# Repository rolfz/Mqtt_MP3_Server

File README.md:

# Mqtt MP3 Player based on Wemos-D1 ESP8266 circuit and VS1053 audio module

## Functionality:

	This module was created to be controlled by Node-Red over a MQTT Broker.
	The module understands various tags such as:
			 /Zaudio/play  "file to play with extension" 8.3 format
			 /Zaudio/volume xxx (volume in db) 0 to 100db is possible
			 /Zaudio/command stop (will stop the file played)
			
	The module also allows to connect a Neoled display module with 7 leds
			 /Zaudio/neoled #xxyyzz  (set color in hex rgb format

## Hardware:
	Wemos D1 module, SPI bus used to communicate with audio module
	
	Adafruit VS1053 module with 3W amplifier PRODUCT ID: 3436
	
	Micro SD card 128mB our larger FAT format.
	
	Connections:
			Wemos D1		-      VS1053   -   Neoled
			D8						MISO
			D7						MOSI
			D5						SCK
			D4						SD-CS
			D6						MP3-CS
			D3						DREQ
			DO						XDCS
			D2									IN
			+5V						AUDIO +5V	5V
			+3V						DIGIT.+3V
	
	! Use min. 5V 2Amp USB to supply both circuits + LED's
		
## Software Libraries:

	Adafruit_Neopixel
	Adafruit_VS1053_Library-master
	pubsubclient (MQTT library)
	
## Software Main file:
	mqtt_mp3_server.ino contains all customized code based on the MQTT client example
	wifi_settings.h 	contains the WIFI private setting

## Using the Zaudio module with Node-red
	Zaudio was tested with a connection to an MQTT brocker running on a RPI3 board
		Software installed was Openhabian with MQTT and Node-red modules installed.

	v1.1 rz 21.2.2018	added OTA code
	v1.0 rz 28.1.2018   orginial code

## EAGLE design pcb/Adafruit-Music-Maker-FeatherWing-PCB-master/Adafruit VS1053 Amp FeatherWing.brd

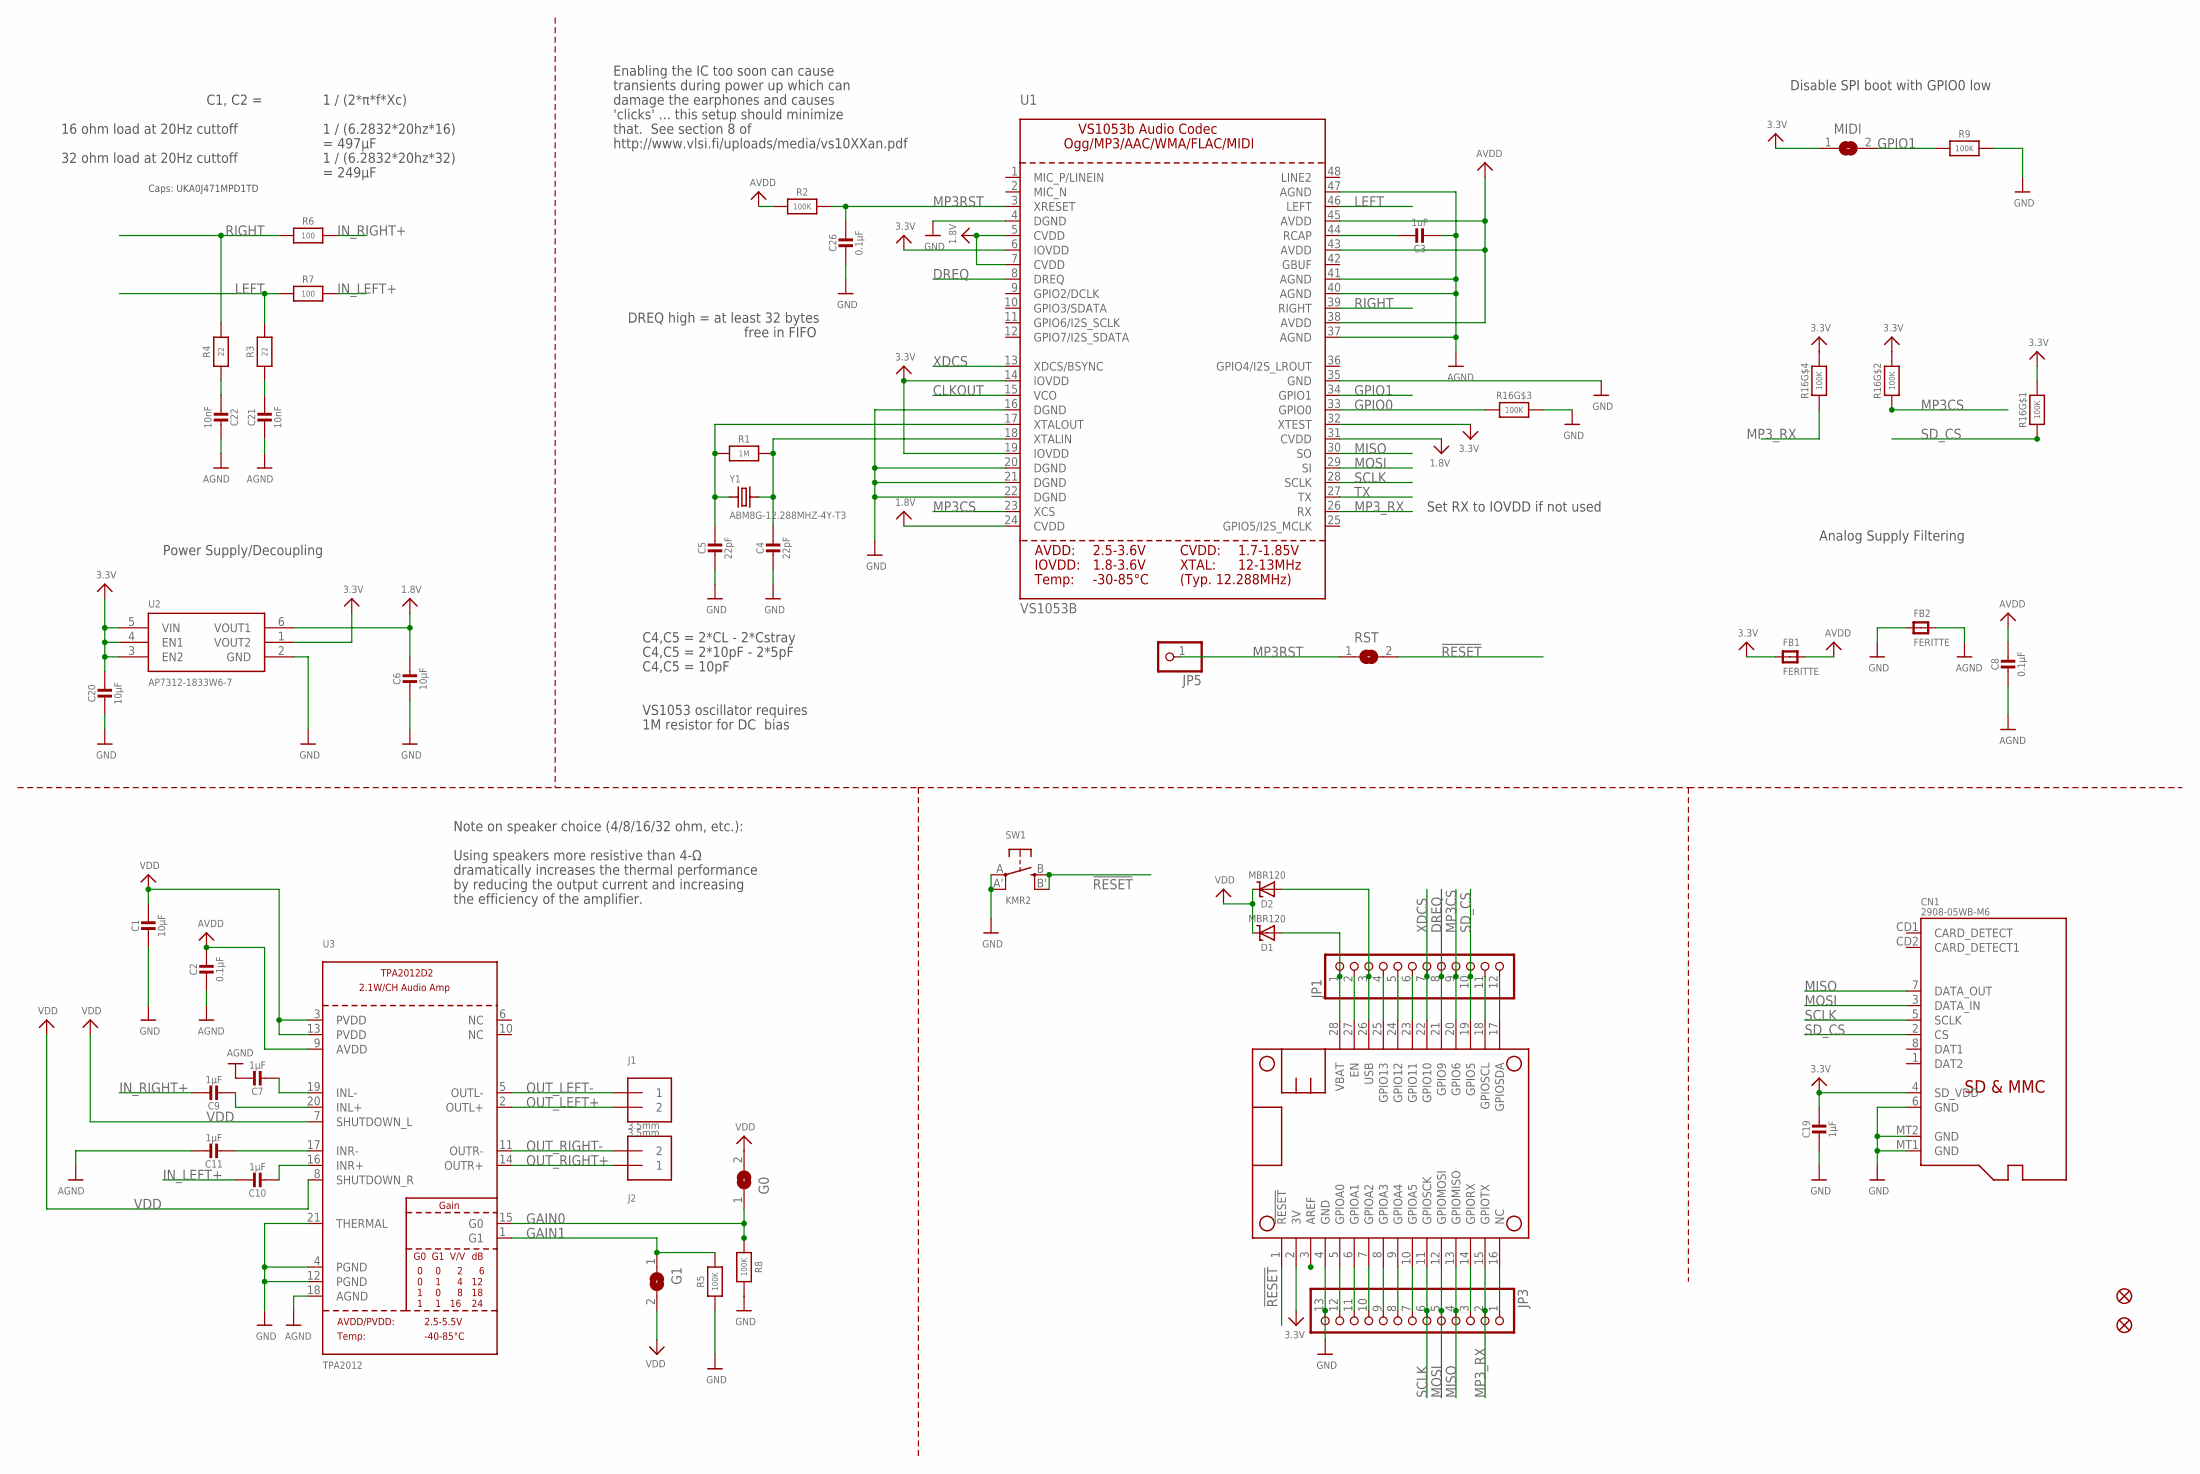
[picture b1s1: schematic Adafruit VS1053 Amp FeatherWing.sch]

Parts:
C1, C20: 10µF; 0805-NO
C2, C8, C26: 0.1µF; 0603-NO
C3: 1uF; 0603-NO
C4, C5: 22pF; 0603-NO
C6: 10µF; _0805MP
C7, C9, C10, C11, C19: 1µF; 0603-NO
C21, C22: 10nF; 0603-NO
CN1: 2908-05WB-M6; MICROSD
D1, D2: MBR120; SOD-123
FB1, FB2: FERITTE; 0805-NO
FID1, FID2: FIDUCIAL""; FIDUCIAL_1MM
G0, G1: SOLDERJUMPER; SOLDERJUMPER_ARROW_NOPASTE
J1, J2: 3.5mm; TERMBLOCK_1X2-3.5MM
JP1: HEADER-1X12; 1X12_ROUND
JP3: HEADER-1X13; 1X13_ROUND_70
JP5: HEADER-1X1ROUND; 1X01_ROUND
MIDI: SOLDERJUMPER; SOLDERJUMPER_ARROW_NOPASTE
MS1: FEATHERWING_NODIM
R1: 1M; 0603-NO
R2, R5, R8: 100K; 0603-NO
R3, R4: 22; 0603-NO
R6, R7: 100; 0603-NO
R9: 100K; _0603MP
R16: 100K; RESPACK_4X0603
RST: SOLDERJUMPERCLOSED; SOLDERJUMPER_CLOSEDWIRE
SW1: KMR2; BTN_KMR2_4.6X2.8
U1: VS1053B; LQFP48
U2: AP7312-1833W6-7; SOT23-6
U3: TPA2012; WQFN20
Y1: ABM8G-12.288MHZ-4Y-T3; CRYSTAL_3.2X2.5

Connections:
1.8V: C6.1, U1.5 (CVDD), U1.7 (CVDD), U1.24 (CVDD), U1.31 (CVDD), U2.6 (VOUT1)
3.3V: C19.1, C20.1, CN1.4 (SD_VDD), FB1.1, MIDI.1, MS1.2 (3V), R16.5 (2), R16.7 (2), R16.8 (2), U1.6 (IOVDD), U1.14 (IOVDD), U1.19 (IOVDD), U1.32 (XTEST), U2.1 (VOUT2), U2.3 (EN2), U2.4 (EN1), U2.5 (VIN)
!RESET: MS1.1 (!RESET), RST.2, SW1.B (S), SW1.B' (S1)
A: JP3.12, MS1.5 (GPIOA0)
AGND: C2.2, C3.2, C7.1, C8.2, C11.1, C21.2, C22.2, FB2.2, U1.37 (AGND), U1.40 (AGND), U1.41 (AGND), U1.47 (AGND), U3.18 (AGND)
AREF: MS1.3 (AREF)
AVDD: C2.1, C8.1, FB1.2, R2.1, U1.38 (AVDD), U1.43 (AVDD), U1.45 (AVDD), U3.9 (AVDD)
B: JP3.11, MS1.6 (GPIOA1)
C: JP3.10, MS1.7 (GPIOA2)
CLKOUT: U1.15 (VCO)
D: JP3.9, MS1.8 (GPIOA3)
DREQ: JP1.8, MS1.21 (GPIO9), U1.8 (DREQ)
E: JP3.8, MS1.9 (GPIOA4)
EN: JP1.2, MS1.27 (EN)
F: JP3.7, MS1.10 (GPIOA5)
G: JP3.1, MS1.16 (NC)
GAIN0: G0.1, R8.1, U3.15 (G0)
GAIN1: G1.1, R5.2, U3.1 (G1)
GND: C1.2, C4.2, C5.2, C6.2, C19.2, C20.2, C26.2, CN1.6 (GND), CN1.MT1 (GND), CN1.MT2 (GND), FB2.1, JP3.13, MS1.4 (GND), R5.1, R8.2, R9.2, R16.6 (2), SW1.A, SW1.A' (P1), U1.4 (DGND), U1.16 (DGND), U1.20 (DGND), U1.21 (DGND), U1.22 (DGND), U1.35 (GND), U2.2 (GND), U3.4 (PGND), U3.12 (PGND), U3.21 (THERMAL)
GPIO0: R16.3 (1), U1.33 (GPIO0)
GPIO1: MIDI.2, R9.1, U1.34 (GPIO1)
IN_LEFT+: C10.1, R7.1
IN_RIGHT+: C9.1, R6.1
L: JP1.6, MS1.23 (GPIO11)
LEFT: R3.1, R7.2, U1.46 (LEFT)
M: JP1.5, MS1.24 (GPIO12)
MISO: CN1.7 (DATA_OUT), JP3.4, MS1.13 (GPIOMISO), U1.30 (SO)
MOSI: CN1.3 (DATA_IN), JP3.5, MS1.12 (GPIOMOSI), U1.29 (SI)
MP3CS: JP1.9, MS1.20 (GPIO6), R16.2 (1), U1.23 (XCS)
MP3RST: C26.1, JP5.1, R2.2, RST.1, U1.3 (XRESET)
MP3_RX: JP3.2, MS1.15 (GPIOTX), R16.4 (1), U1.26 (RX)
N: JP1.4, MS1.25 (GPIO13)
unnamed: C5.1, R1.1, U1.17 (XTALOUT), Y1.1
unnamed: C4.1, R1.2, U1.18 (XTALIN), Y1.2
unnamed: C3.1, U1.44 (RCAP)
unnamed: C21.1, R3.2
unnamed: C22.1, R4.2
unnamed: C9.2, U3.20 (INL+)
unnamed: C7.2, U3.19 (INL-)
unnamed: C11.2, U3.17 (INR-)
unnamed: C10.2, U3.16 (INR+)
OUT_LEFT+: J1.2, U3.2 (OUTL+)
OUT_LEFT-: J1.1, U3.5 (OUTL-)
OUT_RIGHT+: J2.1, U3.14 (OUTR+)
OUT_RIGHT-: J2.2, U3.11 (OUTR-)
RIGHT: R4.1, R6.2, U1.39 (RIGHT)
SCL: JP1.11, MS1.18 (GPIOSCL)
SCLK: CN1.5 (SCLK), JP3.6, MS1.11 (GPIOSCK), U1.28 (SCLK)
SDA: JP1.12, MS1.17 (GPIOSDA)
SD_CS: CN1.2 (CS), JP1.10, MS1.19 (GPIO5), R16.1
TX: U1.27 (TX)
UART_RX: JP3.3, MS1.14 (GPIORX)
USB: D2.A, JP1.3, MS1.26 (USB)
VBAT: D1.A, JP1.1, MS1.28 (VBAT)
VDD: C1.1, D1.C, D2.C, G0.2, G1.2, U3.3 (PVDD), U3.7 (SHUTDOWN_L), U3.8 (SHUTDOWN_R), U3.13 (PVDD)
XDCS: JP1.7, MS1.22 (GPIO10), U1.13 (XDCS/BSYNC)

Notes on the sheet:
Analog Supply Filtering
C4,C5 = 2*CL - 2*Cstray
C4,C5 = 2*10pF - 2*5pF
C4,C5 = 10pF
VS1053 oscillator requires
1M resistor for DC bias
Set RX to IOVDD if not used
DREQ high = at least 32 bytes
Power Supply/Decoupling
transients during power up which can
damage the earphones and causes
'clicks' ... this setup should minimize
that. See section 8 of
http://www.vlsi.fi/uploads/media/vs10XXan.pdf
Enabling the IC too soon can cause
free in FIFO
Disable SPI boot with GPIO0 low
1 / (2*π*f*Xc)
16 ohm load at 20Hz cuttoff
1 / (6.2832*20hz*16)
C1, C2 =
= 497µF
32 ohm load at 20Hz cuttoff
1 / (6.2832*20hz*32)
= 249µF
Caps: UKA0J471MPD1TD
Using speakers more resistive than 4-Ω
dramatically increases the thermal performance
by reducing the output current and increasing
the efficiency of the amplifier.
Note on speaker choice (4/8/16/32 ohm, etc.):

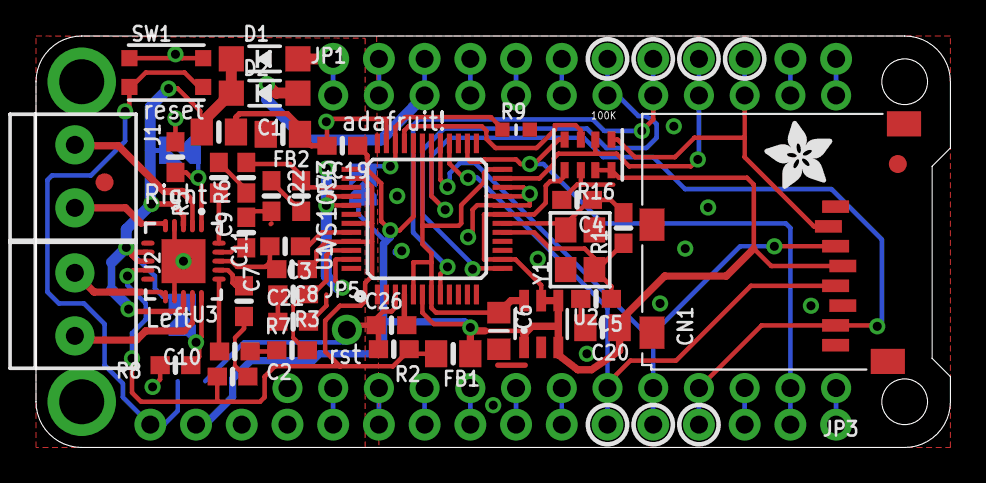
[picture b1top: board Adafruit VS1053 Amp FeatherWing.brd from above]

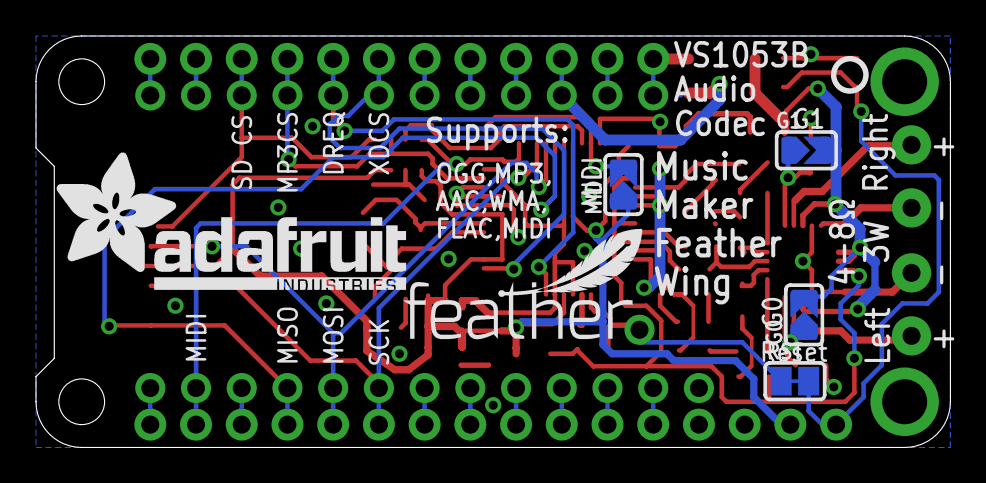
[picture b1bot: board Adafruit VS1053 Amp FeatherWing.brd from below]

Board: 2 copper layers, 50.8 x 22.9 mm, 52 parts (7 on the bottom side), 53 nets.

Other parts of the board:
U$36: ADAFRUIT_3.5MM
U$37: FEATHERLOGO_SMALL
U$43: PCBFEAT-REV-040
U$55: ADAFRUIT_TEXT_20MM

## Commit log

2018-01-29 First Git version of my MQTT Audio Project
2018-01-29 Create README.md
    Documentation will follow
2018-01-29 Added Neoled support for 7 LED's in circle, controlled by mqtt /Zaudio/neoled #xxyyzz color message
2018-01-29 added files for the front page
2018-01-29 update readmy
2018-01-29 added missing files
2018-01-29 no message
2018-01-29 added picture to readme
2018-01-29 updated doc text
2018-01-29 Added node-red picture and text
2018-01-29 added empty wifi-setting file, to be customized by user
2018-02-09 first commit, v1.0 mqtt player
2018-02-09 test
2018-02-12 new commit
2018-02-12 git -n
2018-02-12 upload
2018-02-12 git test
2018-02-12 new test from vcs
2018-02-18 added OTA to MP3 MQTT Player
2018-02-18 added version
2018-02-19 added delay at startup
